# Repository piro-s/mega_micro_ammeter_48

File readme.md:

## Mega micro ammeter 48  
The microammeter is designed to measure small direct currents in low-voltage 
circuits and has the following characteristics:  
+ range of measured currents: 0.05 μA - 500 mA in 6 ranges;  
+ automatic range selection;  
+ results on a display 1602;  
+ building a current graph on a PC (connect via micro USB);  
+ potential at the current measurement point: 0 - 6 V;  
+ power: 5V, via connector micro USB.  
   
Устройство построено на основе статьи

---
#### Scheme:  
[Scheme_v0.2](docs/mega_micro_ammeter_48_v0.2.pdf)  

#### PCB:  

---
#### Gerber:  
Archive for production:  
[gerber_v0.2](https://github.com/piro-s/mega_micro_ammeter_48/raw/main/gerber/mega_micro_ammeter_48_v0.2.zip)

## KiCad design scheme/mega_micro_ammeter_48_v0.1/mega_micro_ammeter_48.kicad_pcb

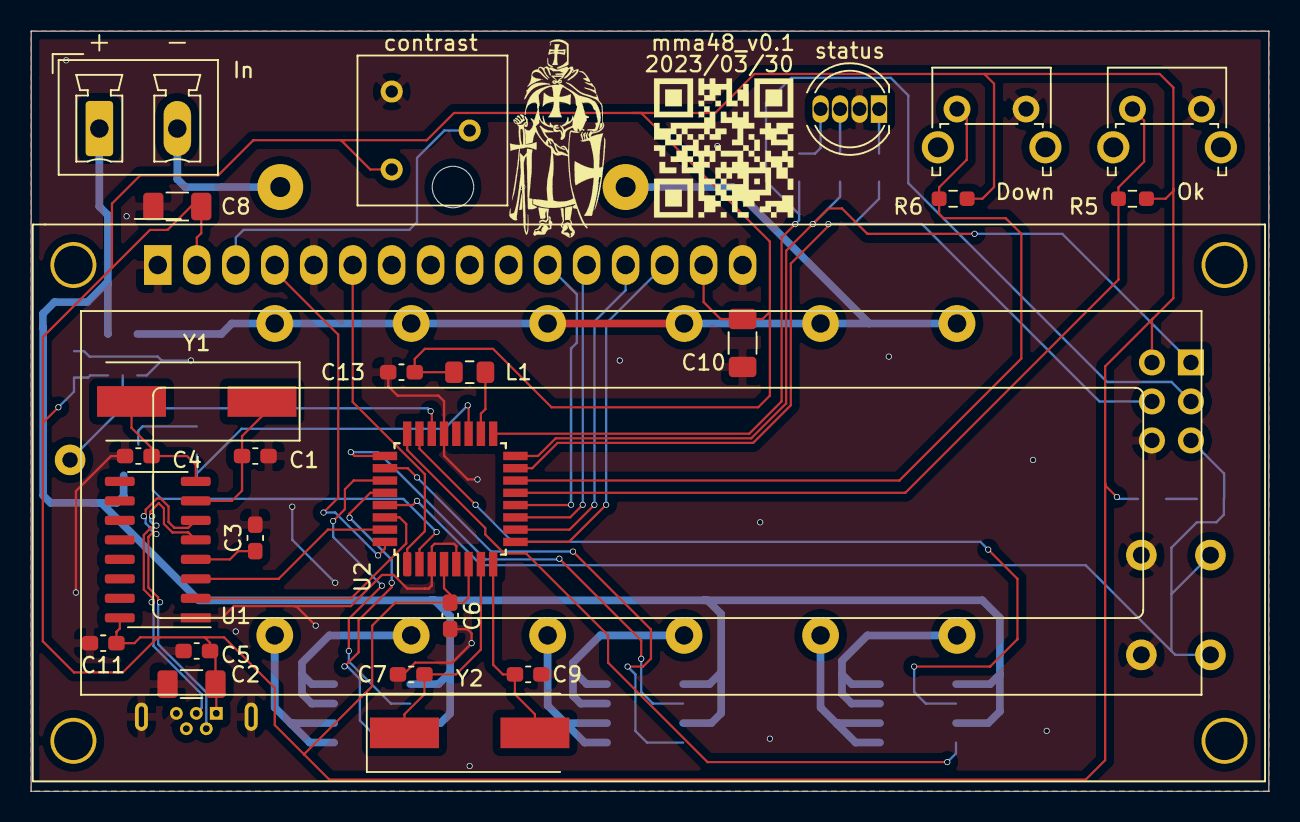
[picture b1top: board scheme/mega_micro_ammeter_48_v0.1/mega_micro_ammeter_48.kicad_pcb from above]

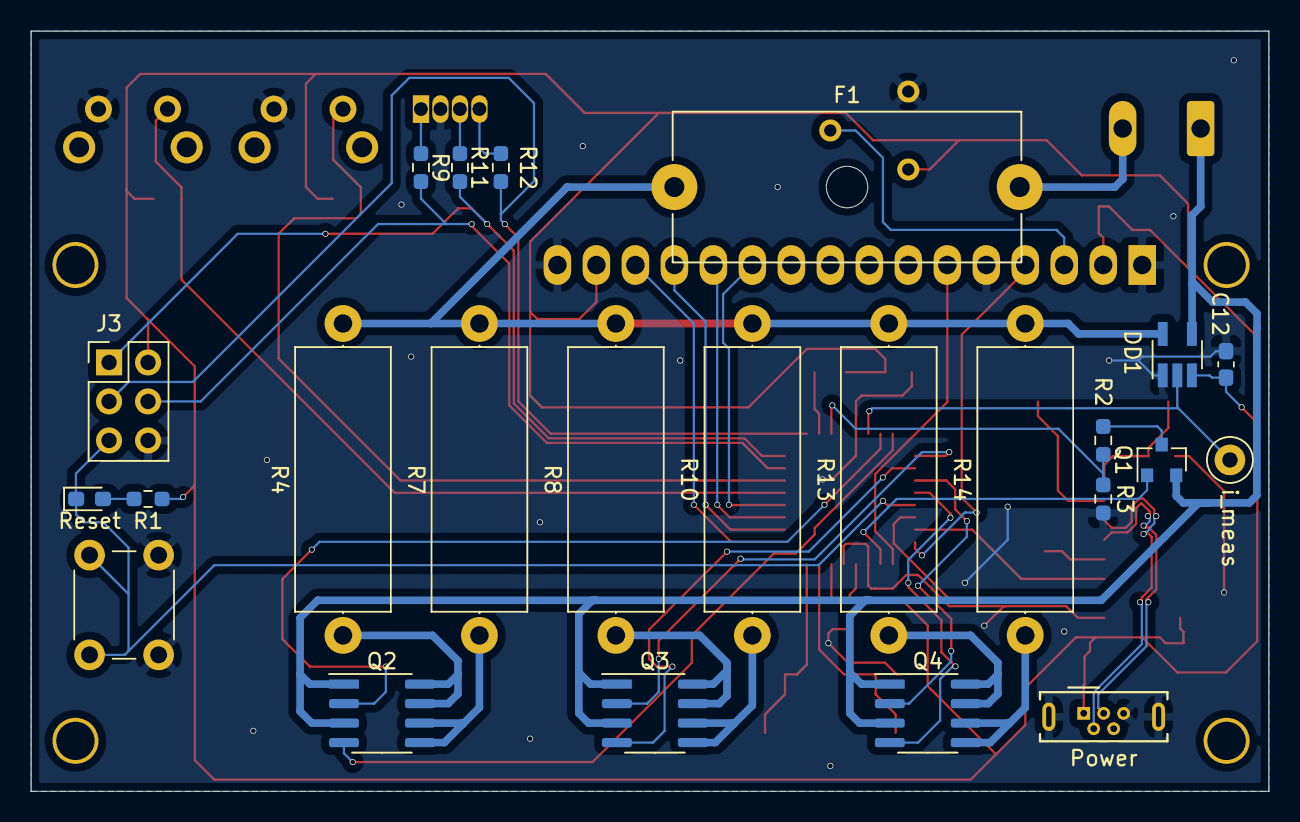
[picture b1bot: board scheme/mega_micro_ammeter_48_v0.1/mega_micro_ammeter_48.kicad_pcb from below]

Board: 2 copper layers, 80.6 x 49.5 mm, 49 parts (24 on the bottom side), 48 nets.

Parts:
C1, C4, C7, C9: 22p; C_0603_1608Metric_Pad1.08x0.95mm_HandSolder
C2, C8, C10: 4.7u; C_1206_3216Metric_Pad1.33x1.80mm_HandSolder
C3: 20n; C_0603_1608Metric_Pad1.08x0.95mm_HandSolder
C5, C6, C11, C12, C13: 100n; C_0603_1608Metric_Pad1.08x0.95mm_HandSolder
D1: Reset; LED_0603_1608Metric_Pad1.05x0.95mm_HandSolder
D2: status; LED_D5.0mm-4_RGB
DD1: MAX4372T; SOT-23-5_HandSoldering
F1: 1A; Fuseholder_Cylinder-5x20mm_Schurter_0031_8201_Horizontal_Op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
J1: Power; USB_Micro-B_Wuerth_614105150721_Vertical
J2: In; PhoenixContact_MCV_1,5_2-G-5.08_1x02_P5.08mm_Vertical
J3: Prog; PinHeader_2x03_P2.54mm_Vertical
L1: 10u; L_0805_2012Metric_Pad1.15x1.40mm_HandSolder
Q1: BSS83P; SOT-23
Q2, Q3, Q4: IRF7324; SOIC-8_3.9x4.9mm_P1.27mm
R1, R11: 560; R_0603_1608Metric_Pad0.98x0.95mm_HandSolder
R2: 1k; R_0603_1608Metric_Pad0.98x0.95mm_HandSolder
R3: 180; R_0603_1608Metric_Pad0.98x0.95mm_HandSolder
R4: 10k; R_Axial_DIN0617_L17.0mm_D6.0mm_P20.32mm_Horizontal
R5, R6: 10k; R_0603_1608Metric_Pad0.98x0.95mm_HandSolder
R7: 1k; R_Axial_DIN0617_L17.0mm_D6.0mm_P20.32mm_Horizontal
R8: 100; R_Axial_DIN0617_L17.0mm_D6.0mm_P20.32mm_Horizontal
R9: 620; R_0603_1608Metric_Pad0.98x0.95mm_HandSolder
R10: 10R; R_Axial_DIN0617_L17.0mm_D6.0mm_P20.32mm_Horizontal
R12: 510; R_0603_1608Metric_Pad0.98x0.95mm_HandSolder
R13: 1R0; R_Axial_DIN0617_L17.0mm_D6.0mm_P20.32mm_Horizontal
R14: 0R1; R_Axial_DIN0617_L17.0mm_D6.0mm_P20.32mm_Horizontal
RV1: 10k; Potentiometer_Bourns_3386F_Vertical
SW1: Reset; SW_PUSH_6mm
SW2: Down; SW_Tactile_SPST_Angled_PTS645Vx39-2LFS
SW3: Ok; SW_Tactile_SPST_Angled_PTS645Vx39-2LFS
TP1: i_meas; TestPoint_Loop_D1.80mm_Drill1.0mm_Beaded
U1: CH340G; SOIC-16_3.9x9.9mm_P1.27mm
U2: ATmega48-20AU; TQFP-32_7x7mm_P0.8mm
U3: RC1602A; WC1602A
Y1: 12MHz; Crystal_SMD_HC49-SD
Y2: 8MHz; Crystal_SMD_HC49-SD

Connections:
+5V: C2.1, C5.1, C6.1, C8.1, C10.1, C11.1, C12.1, C13.1, DD1.3, J1.1, J3.2, L1.1, R1.1, R5.1, R6.1, RV1.1, U1.16, U2.4, U2.6, U3.2, U3.15
/btn_down: R6.2, SW2.1, U2.14
/btn_ok: R5.2, SW3.1, U2.13
/i_in: DD1.4, J2.1, Q1.2, Q2.1, Q2.3, Q3.1, Q3.3, Q4.1, Q4.3
/i_meas: DD1.2, TP1.1, U2.22
/i_out: F1.2, J2.2
/lcd_db4: U2.12, U3.11
/lcd_db5: U2.11, U3.12
/lcd_db6: U2.10, U3.13
/lcd_db7: U2.9, U3.14
/lcd_en: U2.1, U3.6
/lcd_rs: U2.32, U3.4
/led_b: J3.3, R12.1, U2.17
/led_g: J3.1, R11.1, U2.16
/led_r: J3.4, R9.1, U2.15
/r_1: Q2.2, U2.23
/r_2: Q2.4, U2.24
/r_3: Q3.2, U2.25
/r_4: Q3.4, U2.26
/r_5: Q4.2, U2.27
/r_6: Q4.4, U2.28
/reset: D1.1, J3.5, SW1.1, U2.29
/tr_v_in: Q1.1, U2.2
/uart_rx: U1.2, U2.30
/uart_tx: U1.3, U2.31
/usb+: J1.3, U1.5
/usb-: J1.2, U1.6
/v_in: R2.2, R3.1, U2.19
/v_sense_n: DD1.5, F1.1, R4.2, R7.2, R8.2, R10.2, R13.2, R14.2
/xtal_1: C7.1, U2.7, Y2.1
/xtal_2: C9.1, U2.8, Y2.2
GND: C1.2, C2.2, C3.2, C4.2, C5.2, C6.2, C7.2, C8.2, C9.2, C10.2, C11.2, C12.2, C13.2, D2.2, DD1.1, J1.5, J1.6, J3.6, R3.2, RV1.3, SW1.2, SW2.2, SW3.2, U1.1, U2.3, U2.5, U2.21, U3.1, U3.5, U3.16
unnamed: C1.1, U1.7, Y1.1
unnamed: C3.1, U1.4
unnamed: C4.1, U1.8, Y1.2
unnamed: D1.2, R1.2
unnamed: D2.1, R9.2
unnamed: D2.3, R11.2
unnamed: D2.4, R12.2
unnamed: Q1.3, R2.1
unnamed: Q2.5, Q2.6, R7.1
unnamed: Q2.7, Q2.8, R4.1
unnamed: Q3.5, Q3.6, R10.1
unnamed: Q3.7, Q3.8, R8.1
unnamed: Q4.5, Q4.6, R14.1
unnamed: Q4.7, Q4.8, R13.1
unnamed: RV1.2, U3.3
VDDA: L1.2, U2.18

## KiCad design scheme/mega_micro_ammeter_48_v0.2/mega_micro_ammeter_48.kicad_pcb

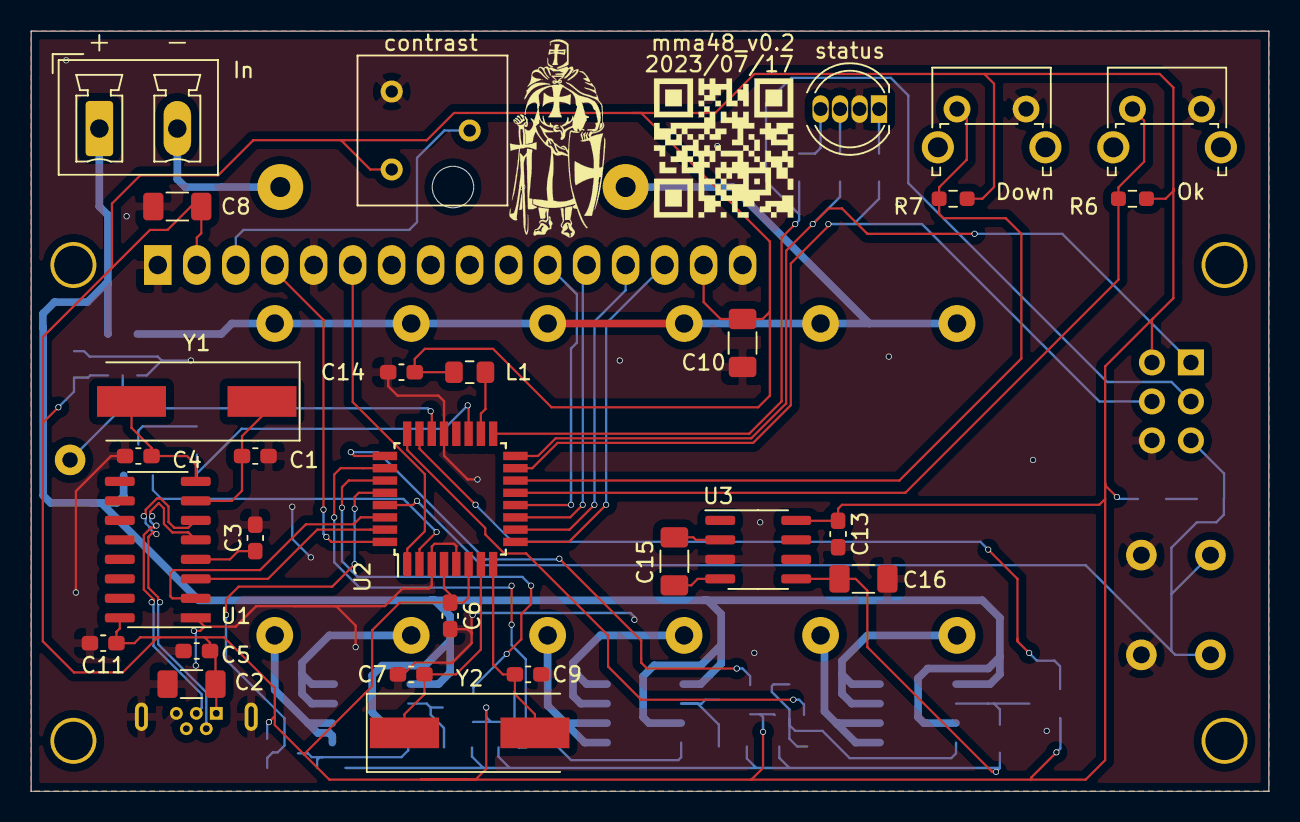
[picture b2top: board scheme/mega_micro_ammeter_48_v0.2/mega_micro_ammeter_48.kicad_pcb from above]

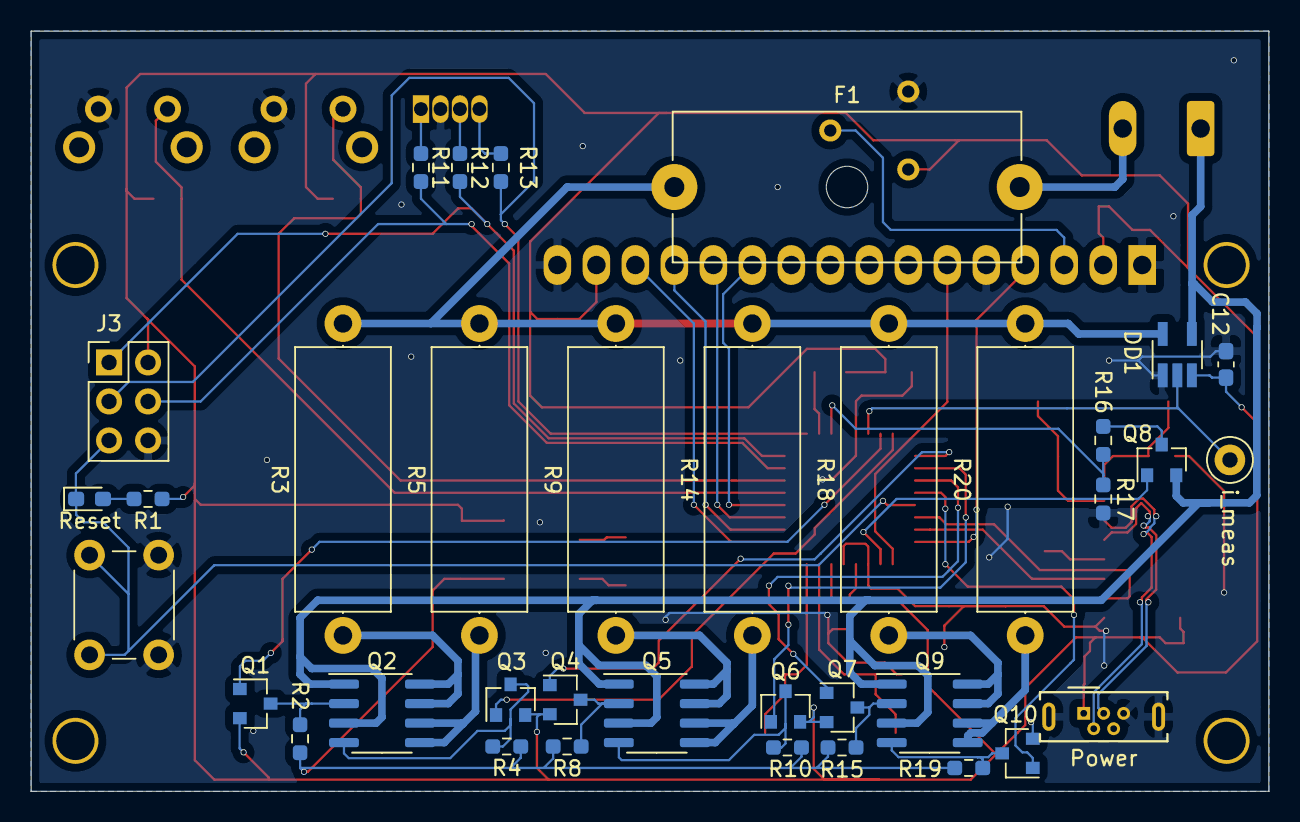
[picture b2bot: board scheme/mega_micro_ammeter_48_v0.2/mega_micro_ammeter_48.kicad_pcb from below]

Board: 2 copper layers, 80.6 x 49.5 mm, 65 parts (36 on the bottom side), 57 nets.

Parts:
C1, C4, C7, C9: 22p; C_0603_1608Metric_Pad1.08x0.95mm_HandSolder
C2, C8, C10: 4.7u; C_1206_3216Metric_Pad1.33x1.80mm_HandSolder
C3: 20n; C_0603_1608Metric_Pad1.08x0.95mm_HandSolder
C5, C6, C11, C12, C13, C14: 100n; C_0603_1608Metric_Pad1.08x0.95mm_HandSolder
C15, C16: 10u; C_1206_3216Metric_Pad1.33x1.80mm_HandSolder
D1: Reset; LED_0603_1608Metric_Pad1.05x0.95mm_HandSolder
D2: status; LED_D5.0mm-4_RGB
DD1: MAX4372T; SOT-23-5_HandSoldering
F1: 1A; Fuseholder_Cylinder-5x20mm_Schurter_0031_8201_Horizontal_Op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
J1: In; PhoenixContact_MCV_1,5_2-G-5.08_1x02_P5.08mm_Vertical
J2: Power; USB_Micro-B_Wuerth_614105150721_Vertical
J3: Prog; PinHeader_2x03_P2.54mm_Vertical
L1: 10u; L_0805_2012Metric_Pad1.15x1.40mm_HandSolder
Q1, Q3, Q4, Q6, Q7, Q8, Q10: AO3401A; SOT-23
Q2, Q5, Q9: IRF7324; SOIC-8_3.9x4.9mm_P1.27mm
R1, R12: 560; R_0603_1608Metric_Pad0.98x0.95mm_HandSolder
R2, R4, R6, R7, R8, R10, R15, R19: 10k; R_0603_1608Metric_Pad0.98x0.95mm_HandSolder
R3: 10k; R_Axial_DIN0617_L17.0mm_D6.0mm_P20.32mm_Horizontal
R5: 1k; R_Axial_DIN0617_L17.0mm_D6.0mm_P20.32mm_Horizontal
R9: 100; R_Axial_DIN0617_L17.0mm_D6.0mm_P20.32mm_Horizontal
R11: 620; R_0603_1608Metric_Pad0.98x0.95mm_HandSolder
R13: 510; R_0603_1608Metric_Pad0.98x0.95mm_HandSolder
R14: 10R; R_Axial_DIN0617_L17.0mm_D6.0mm_P20.32mm_Horizontal
R16: 1k; R_0603_1608Metric_Pad0.98x0.95mm_HandSolder
R17: 180; R_0603_1608Metric_Pad0.98x0.95mm_HandSolder
R18: 1R0; R_Axial_DIN0617_L17.0mm_D6.0mm_P20.32mm_Horizontal
R20: 0R1; R_Axial_DIN0617_L17.0mm_D6.0mm_P20.32mm_Horizontal
RV1: 10k; Potentiometer_Bourns_3386F_Vertical
SW1: Reset; SW_PUSH_6mm
SW2: Down; SW_Tactile_SPST_Angled_PTS645Vx39-2LFS
SW3: Ok; SW_Tactile_SPST_Angled_PTS645Vx39-2LFS
TP1: i_meas; TestPoint_Loop_D1.80mm_Drill1.0mm_Beaded
U1: CH340G; SOIC-16_3.9x9.9mm_P1.27mm
U2: ATmega48-20AU; TQFP-32_7x7mm_P0.8mm
U3: TC7660; SOIC-8_3.9x4.9mm_P1.27mm
U4: RC1602A; display_1602_nofootprint
Y1: 12MHz; Crystal_SMD_HC49-SD
Y2: 14.7456MHz; Crystal_SMD_HC49-SD

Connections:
+5V: C2.1, C5.1, C6.1, C8.1, C10.1, C11.1, C12.1, C13.1, C14.1, DD1.3, J2.1, J3.2, L1.1, Q1.2, Q3.2, Q4.2, Q6.2, Q7.2, Q10.2, R1.1, R6.1, R7.1, RV1.1, U1.16, U2.4, U2.6, U3.8, U4.2, U4.15
-5V: C16.1, R2.2, R4.2, R8.2, R10.2, R15.2, R19.2, U3.5
/btn_down: R7.2, SW2.1, U2.14
/btn_ok: R6.2, SW3.1, U2.13
/i_in: DD1.4, J1.1, Q2.1, Q2.3, Q5.1, Q5.3, Q8.2, Q9.1, Q9.3
/i_meas: DD1.2, TP1.1, U2.22
/i_out: F1.2, J1.2
/lcd_db4: U2.12, U4.11
/lcd_db5: U2.11, U4.12
/lcd_db6: U2.10, U4.13
/lcd_db7: U2.9, U4.14
/lcd_en: U2.1, U4.6
/lcd_rs: U2.32, U4.4
/led_b: J3.3, R13.1, U2.17
/led_g: J3.1, R12.1, U2.16
/led_r: J3.4, R11.1, U2.15
/r_1: Q1.1, U2.23
/r_2: Q3.1, U2.24
/r_3: Q4.1, U2.25
/r_4: Q6.1, U2.26
/r_5: Q7.1, U2.27
/r_6: Q10.1, U2.28
/reset: D1.1, J3.5, SW1.1, U2.29
/tr_v_in: Q8.1, U2.2
/uart_rx: U1.2, U2.30
/uart_tx: U1.3, U2.31
/usb+: J2.3, U1.5
/usb-: J2.2, U1.6
/v_in: R16.2, R17.1, U2.19
/v_sense_n: DD1.5, F1.1, R3.2, R5.2, R9.2, R14.2, R18.2, R20.2
/xtal_1: C7.1, U2.7, Y2.1
/xtal_2: C9.1, U2.8, Y2.2
GND: C1.2, C2.2, C3.2, C4.2, C5.2, C6.2, C7.2, C8.2, C9.2, C10.2, C11.2, C12.2, C13.2, C14.2, C16.2, D2.2, DD1.1, J2.5, J2.6, J3.6, R17.2, RV1.3, SW1.2, SW2.2, SW3.2, U1.1, U2.3, U2.5, U2.21, U3.3, U4.1, U4.5, U4.16
unnamed: C1.1, U1.7, Y1.1
unnamed: C3.1, U1.4
unnamed: C4.1, U1.8, Y1.2
unnamed: C15.1, U3.2
unnamed: C15.2, U3.4
unnamed: D1.2, R1.2
unnamed: D2.1, R11.2
unnamed: D2.3, R12.2
unnamed: D2.4, R13.2
unnamed: Q1.3, Q2.2, R2.1
unnamed: Q2.4, Q3.3, R4.1
unnamed: Q2.5, Q2.6, R5.1
unnamed: Q2.7, Q2.8, R3.1
unnamed: Q4.3, Q5.2, R8.1
unnamed: Q5.4, Q6.3, R10.1
unnamed: Q5.5, Q5.6, R14.1
unnamed: Q5.7, Q5.8, R9.1
unnamed: Q7.3, Q9.2, R15.1
unnamed: Q8.3, R16.1
unnamed: Q9.5, Q9.6, R20.1
unnamed: Q9.7, Q9.8, R18.1
unnamed: Q9.4, Q10.3, R19.1
unnamed: RV1.2, U4.3
VDDA: L1.2, U2.18

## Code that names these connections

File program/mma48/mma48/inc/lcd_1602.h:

/*
 * lcd_1602.h
 *
 * Library for LCD 1602.
 * 
 * Library information:
 * - 4 bit data (change pins in defines if needed).
 * - font 5x8;
 * - no display shift. 
 *
 * Created: 12.04.2023 10:40:12
 *  Author: piro.tex
 */ 

#ifndef __lcd_1602_h__
#define __lcd_1602_h__

///--- includes
#include <avr/io.h>
#include "main.h"


///--- defines
#define lcd_rs_port_set DDRD
#define lcd_rs_port PORTD
#define lcd_rs_pin 2

#define lcd_e_port_set DDRD
#define lcd_e_port PORTD
#define lcd_e_pin 3

#define lcd_db4_port_set DDRB
#define lcd_db4_port PORTB
#define lcd_db4_pin 0
#define lcd_db5_port_set DDRD
#define lcd_db5_port PORTD
#define lcd_db5_pin 7
#define lcd_db6_port_set DDRD
#define lcd_db6_port PORTD
#define lcd_db6_pin 6
#define lcd_db7_port_set DDRD
#define lcd_db7_port PORTD
#define lcd_db7_pin 5


///--- enums
enum lcd
{
    lcd_rs_c        = PinReset, // LCD command
    lcd_rs_d        = PinSet, // LCD data
    
    lcd_row         = 2, // LCD row
    lcd_column      = 16, // LCD column
};


///--- functions
void lcd_write_4bit(uint8_t data); // Send data (4 bits)
void lcd_write(uint8_t rs, uint8_t data); // Send data or command
void lcd_init(void); // Init LCD

void lcd_set_cursor(uint8_t r, uint8_t c); // Set cursor
void lcd_print_symbol(char symbol); // Print symbol
void lcd_print_string(char* string); // Print string
void lcd_print_uint(uint32_t value); // Print uint16_t
void lcd_print_float(float value); // Print float
void lcd_clear(void); // Clear LCD output
void lcd_clear_area(uint8_t r, uint8_t c, uint8_t length); // Clear LCD area


#endif // __lcd_1602_h__

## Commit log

2023-08-24 Initial
